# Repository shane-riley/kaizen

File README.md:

# kaizen

My repository of coursework, practice problems and 'continuous improvement'. This repo includes all code written that is not copyright for research, employment, or wrapped into personal or team projects.

The purpose of storing this code is to witness my own growth as a programmer, to use as motivation to keep striving to improve.

__NOTE: THIS REPO IS STILL UNDER CONSTRUCTION__

## classes

Code from coursework, from the very beginning of my programming journey. The projects have been whitelabeled and sections have been removed to avoid copyright issues and discourage plagiarism.

Folders:

- java: Intermediate Java (taken at community college)
- ds_1: Data Structures/Algs 1 (Hashing, Sorting, List-type structures, etc.)
- ds_2: Data Structures/Algs 2 (Trees, Tries, Compression, Heaps, etc.)
- al: Introduction to Assembly Language (MIPS, leveraging the MARS dialect)
- nm: Numerical Methods in MATLAB
- ss: Systems Software (C and x86)
- gp: Graphics Programming (C and OpenGL)
- os: Operating systems
- ml: Machine learning
- cv: Computer vision
- mech: Mechatronics

## problems

- leetcode: Leetcode problems
- project_euler: Project Euler problems

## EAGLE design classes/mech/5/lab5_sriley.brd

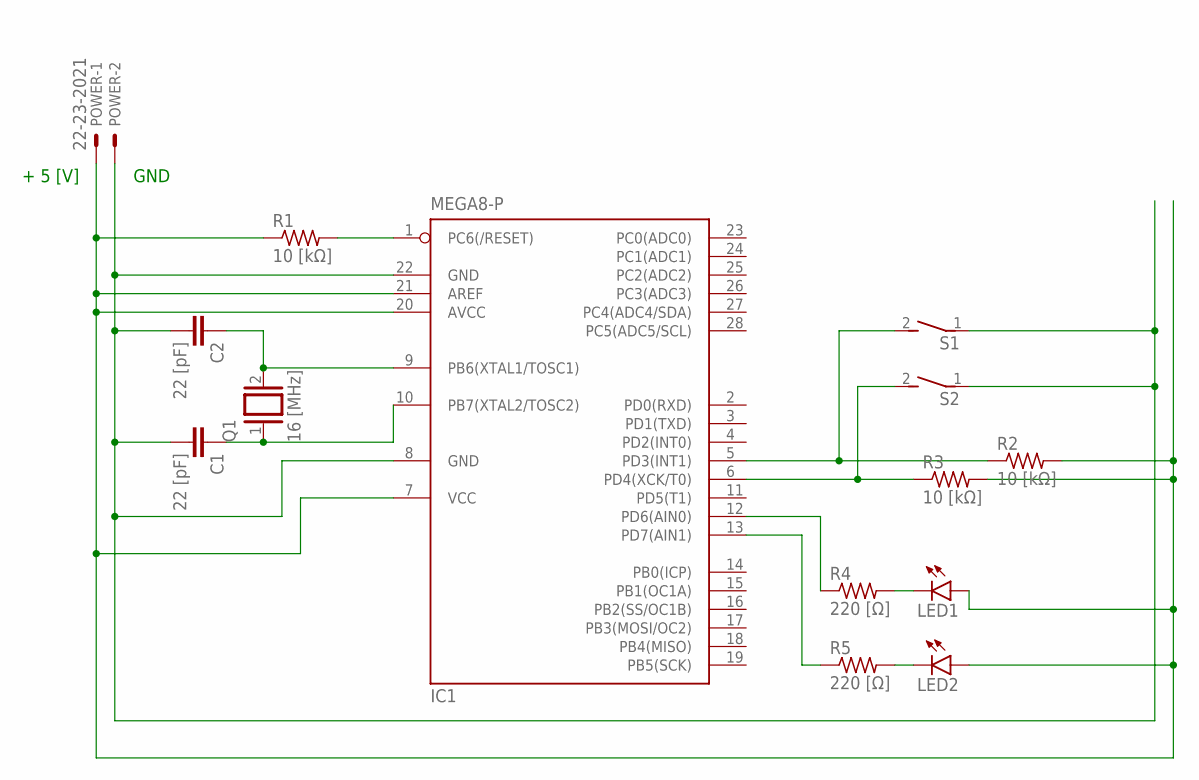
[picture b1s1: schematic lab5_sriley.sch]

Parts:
C1, C2: 22 [pF]; C2.5-3
IC1: MEGA8-P; DIL28-3
LED1, LED2: LED5MM
POWER: 22-23-2021
Q1: 16 [MHz]; Q
R1, R2, R3: 10 [kΩ]; 0204/7
R4, R5: 220 [Ω]; 0204/7
S1, S2: DS01E; DS-01

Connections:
unnamed: C2.1, IC1.9 (PB6(XTAL1/TOSC1)), Q1.2
unnamed: C1.1, IC1.10 (PB7(XTAL2/TOSC2)), Q1.1
unnamed: C1.2, C2.2, IC1.8 (GND), IC1.22 (GND), POWER.2, S1.1, S2.1
unnamed: IC1.7 (VCC), IC1.20 (AVCC), IC1.21 (AREF), LED1.A, LED2.A, POWER.1, R1.1, R2.2, R3.2
unnamed: IC1.1 (PC6(/RESET)), R1.2
unnamed: IC1.5 (PD3(INT1)), R2.1, S1.2
unnamed: IC1.6 (PD4(XCK/T0)), R3.1, S2.2
unnamed: LED1.K (C), R4.2
unnamed: LED2.K (C), R5.2
unnamed: IC1.12 (PD6(AIN0)), R4.1
unnamed: IC1.13 (PD7(AIN1)), R5.1

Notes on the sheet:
GND
+ 5 [V]

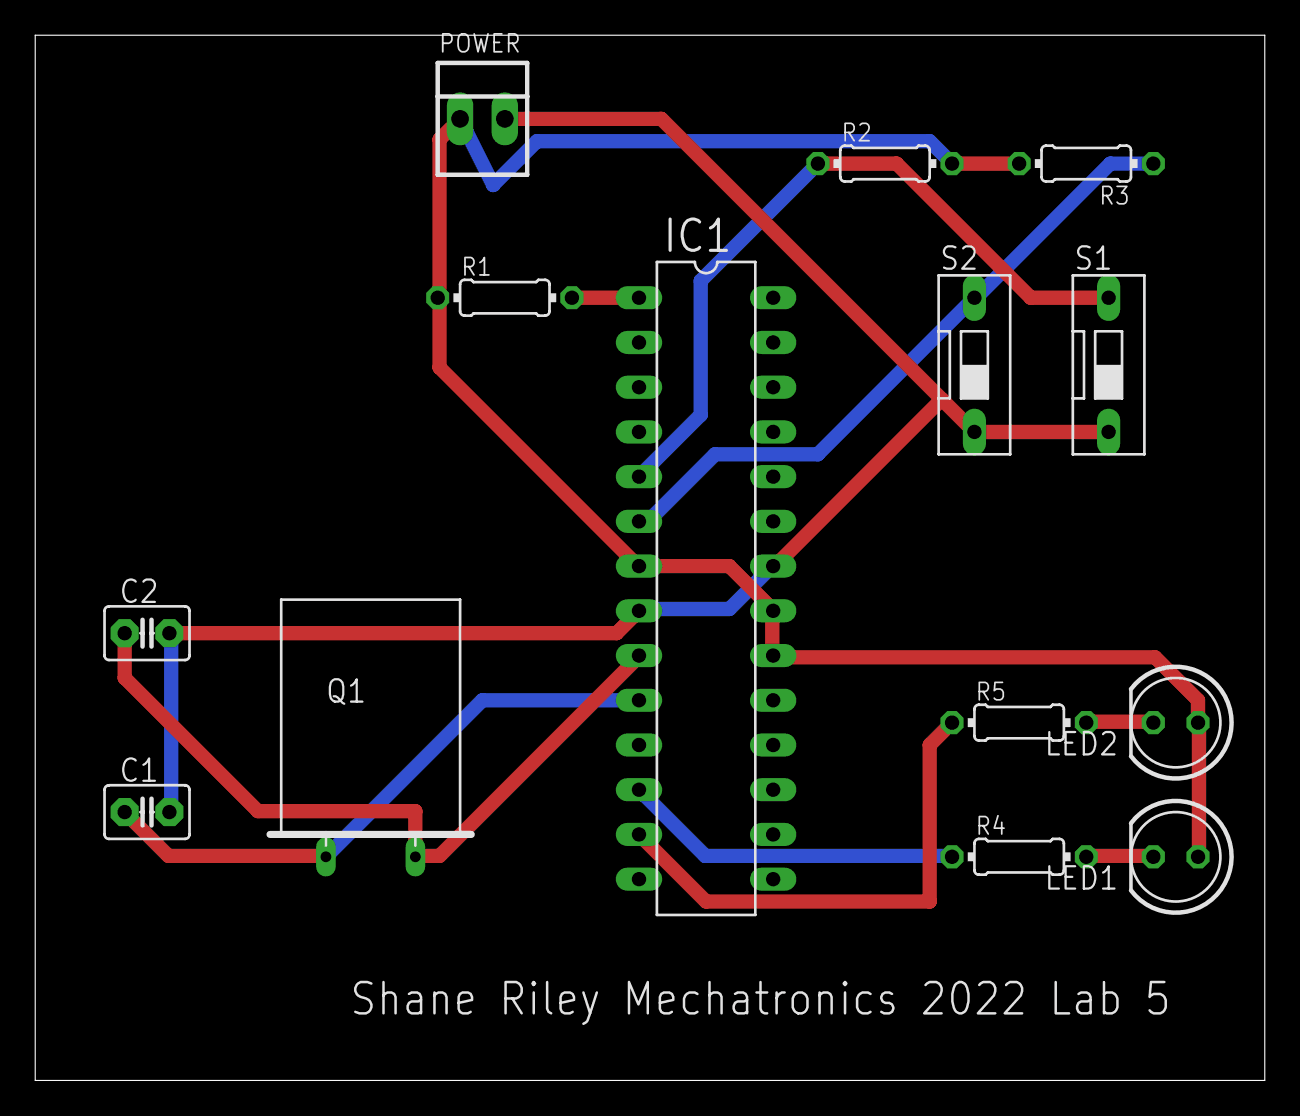
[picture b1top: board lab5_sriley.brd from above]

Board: 2 copper layers, 69.8 x 59.4 mm, 14 parts (0 on the bottom side), 11 nets.

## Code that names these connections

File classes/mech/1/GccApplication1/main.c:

/*
 * lab1_2020.cpp
 *
 * Created: 1/9/2020 Based on Lab_1_2019
 * Author : WWClark
 */ 

/*
This program is a solution to Lab 1 -- 
	Pushbutton switches are connected to Pins PD3 and PD4 (pulled high when switch is open).
	LEDs are connected to Pins PD6 and PD7 (active low). 
	
	The program causes the LEDs to mimic the input pin states (i.e. when Pin PD3 is high, the LED connected to Pin PD6 is on.  Likewise for Pins PD4 and PD7).

*/

#include <avr/io.h>

int main(void)
{
	 	
	DDRD = 0b11000000;  // set bits PD7-PD6 as output, PD5-PD0 as input (this covers Pins 3 and 4 as needed for inputs, and 6 and 7 as needed for outputs)
		// Follows a practice of making unused pins to be input (safer)
	PORTD = 0b11000000; // set output bits on PORTD so that all outputs are off (they are wired as active low)
		 
    // ============================================
    // P R O G R A M L O O P
    // ============================================
	while(1)
    {
				
       	if (PIND & 0b00001000) // Check the status of Switch 1.  
		   // This line checks the switch status by doing a Boolean operation between PIND (where the switch is connected) and a binary number that targets the 
		   // single pin that we are trying to read (Pin 3). For more on Boolean operations and "single bit addressing", see the C Programming slides.
		   // The argument of the If is TRUE only if the switch is closed (and Pin3 is a high voltage), in which case we want to turn on LED 1.
		{
			PORTD = PORTD & 0b10111111; // Turn on LED 1. 
			// This line uses more Boolean arithmetic to clear pin PD6 while leaving the other bits on PORTD unchanged.  Specifically, the line computes
			// a logical AND between the existing PORTD values and a binary number that has 0 in the only bit that we want to ensure is 0, PD6.  All other bits remain
			// unchanged (i.e. this line does not affect bit PD7, the other LED).
			// The result is that since the LED on pin 6 of PORTD is wired as active low, this line causes it to turn on.
		}
		else 
		{
			PORTD = PORTD | 0b01000000;  // Turn off LED 1. 
			// More Boolean arithmetic to cause PD6 to go high (a logical OR is performed between data in PORTD and a binary number that targets pin PD6), 
			// which causes LED 1 to be off and other bits, specifically LED 2, are unchanged.
		}
		// Repeat for LED and Switch 2
		if (PIND & 0b00010000) // Check the status of Switch 2.
			// Same as above but pin PD4 is the target.
		{
			PORTD = PORTD & 0b01111111;  // Turn on LED 2.
			// Same as in first If but pin PD7 is the target.
		}
		else 
		{
			PORTD = PORTD | 0b10000000; // Turn off LED 2.
			// Same as in first Else but pin PD7 is the target.
		}
		
	}
	
return 0;	
}
// ============================================
// S U B R O U T I N E S
// ============================================

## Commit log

2021-10-18 Coursework before this semester
2021-10-18 Construction notice
2022-01-08 Fall 2021 projects
2022-02-19 Starter problems
2022-05-01 Truncate history
2022-05-01 Mechatronics
2022-06-01 Daily leetcode
2022-06-02 More daily leetleetcode
2022-07-14 Blind 75 array subset
